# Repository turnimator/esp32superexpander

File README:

ESP32Superexpander.2ndattempt  - Previous hardware definition (KiCad) files
ESP32forth-7-Superexpander-0.1 - Arduino sketch containing a Superexpander ESPforth version
ESP32superexpander       -  The current Kicad files
Superexpander            - Arduino library for Suoerexpander
SuperExpander.odt        - A description of the project
superexpanderSupport.c   - Code to add to ESP32forth 

A document explaining the Forth code:

https://docs.google.com/document/d/1MlfXAm6yeVxjHgzF-E0LGG0kIZ7gFkiAXZAdYF-DrEk/edit?usp=sharing

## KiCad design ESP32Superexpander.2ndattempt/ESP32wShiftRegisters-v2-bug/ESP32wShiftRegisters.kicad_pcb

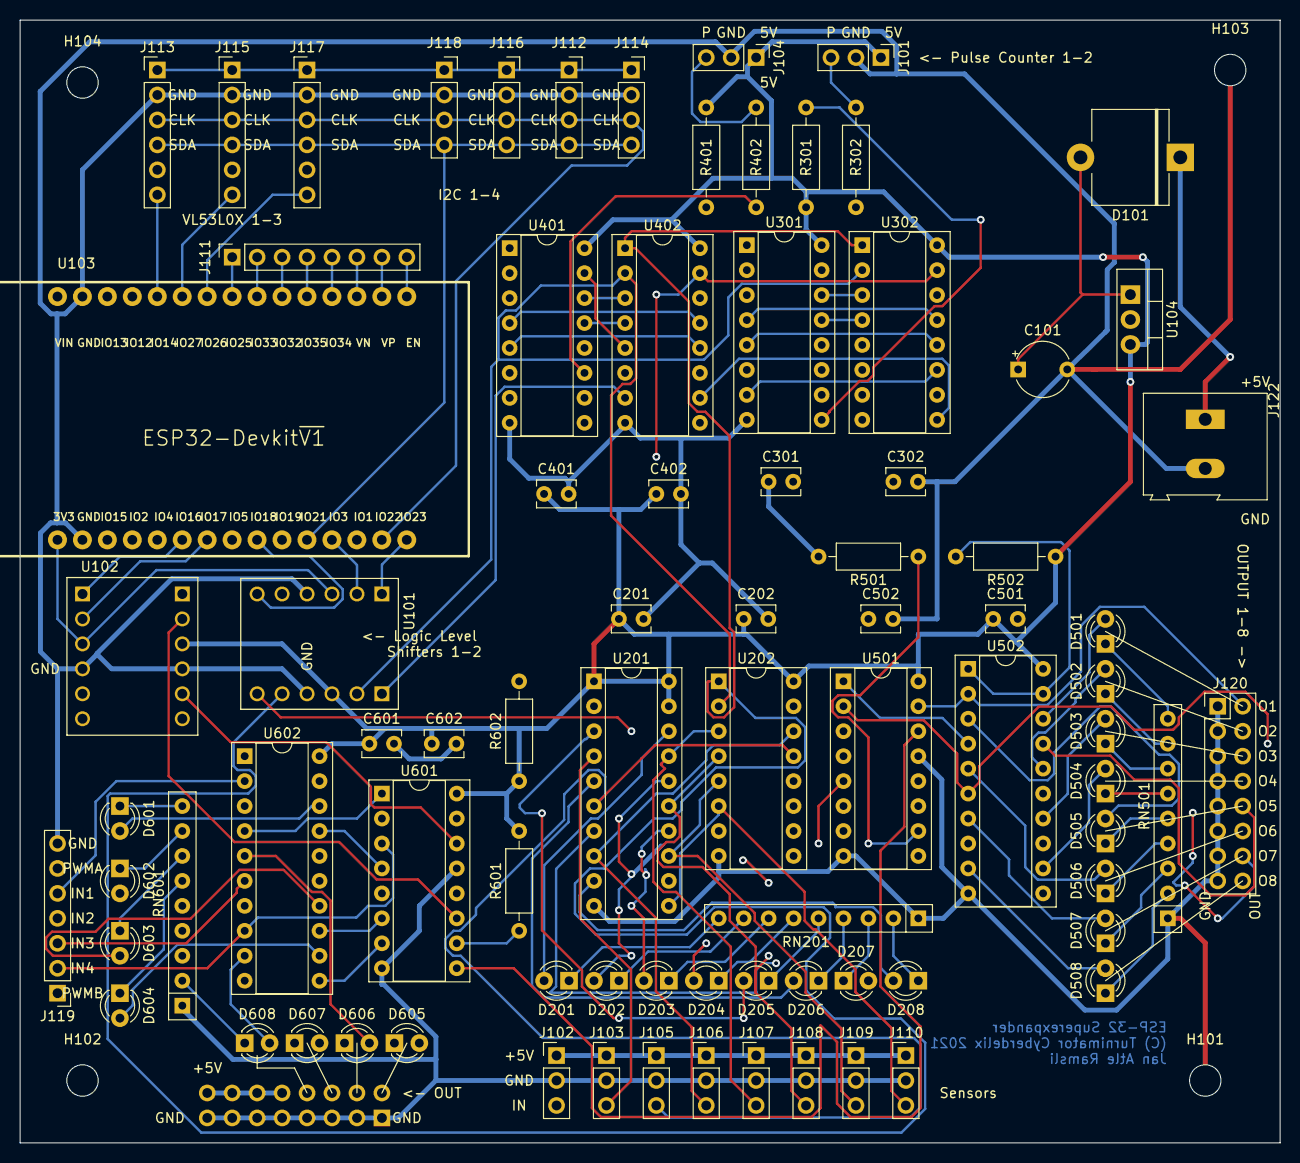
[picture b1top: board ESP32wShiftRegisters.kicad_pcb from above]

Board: 4 copper layers, 128.2 x 114.3 mm, 87 parts (1 on the bottom side), 137 nets.

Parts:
C101: 100uF; CP_Radial_Tantal_D5.5mm_P5.00mm
C201, C202: 100 nF; C_Disc_D3.8mm_W2.6mm_P2.50mm
C301, C302, C401, C402, C501, C502, C601, C602: 0.10uF; C_Disc_D3.8mm_W2.6mm_P2.50mm
D101: DIODE; D_5KP_P10.16mm_Horizontal
D201, D202, D203, D204, D205, D206, D207, D208, D501, D502, D503, D504, D505, D506, D507, D508, D601, D602, D603, D604, D605, D606, D607, D608: LED; LED_D3.0mm
H101, H102, H104: NC; MountingHole_3.2mm_M3
H103: GND; MountingHole_3.2mm_M3
J101: CNT1_in; PinHeader_1x03_P2.54mm_Vertical
J102: S1; PinHeader_1x03_P2.54mm_Vertical
J103: S2; PinHeader_1x03_P2.54mm_Vertical
J104: CNT2_in; PinHeader_1x03_P2.54mm_Vertical
J105: S3; PinHeader_1x03_P2.54mm_Vertical
J106: S4; PinHeader_1x03_P2.54mm_Vertical
J107: S5; PinHeader_1x03_P2.54mm_Vertical
J108: S6; PinHeader_1x03_P2.54mm_Vertical
J109: S7; PinHeader_1x03_P2.54mm_Vertical
J110: S8; PinHeader_1x03_P2.54mm_Vertical
J111: EN VP VN 34 35 32 33 25; PinSocket_1x08_P2.54mm_Vertical
J112, J116, J118: I2C; PinSocket_1x04_P2.54mm_Vertical
J113: VL53L0X_1; PinHeader_1x06_P2.54mm_Vertical
J114: i2C; PinSocket_1x04_P2.54mm_Vertical
J115: VL53L0X_2; PinHeader_1x06_P2.54mm_Vertical
J117: VL53L0X_3; PinHeader_1x06_P2.54mm_Vertical
J119: L298; PinHeader_1x07_P2.54mm_Vertical
J120: OUTPUT->; PinHeader_2x08_P2.54mm_Vertical
J121: Conn_02x08_Odd_Even; PinHeader_2x08_P2.54mm_Vertical
J122: 5V POWER; TerminalBlock_Altech_AK300-2_P5.00mm
R301, R302, R401, R402, R501, R502, R601, R602: 10k; R_Axial_DIN0207_L6.3mm_D2.5mm_P10.16mm_Horizontal
RN201, RN501, RN601: 220 R; R_Array_SIP9
U101, U102: BOB-12009; CONV_BOB-12009
U103: ESP32DEVKITV1; ESP32-DEVKITV1
U104: L7805; TO-220-3_Vertical
U201, U502, U602: 74HC244; DIP-20_W7.62mm_Socket
U202, U302, U402: 74LS165; DIP-16_W7.62mm_Socket
U301, U401: CD4060BE; DIP-16_W7.62mm_Socket
U501, U601: 74LS595; DIP-16_W7.62mm_Socket

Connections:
3VCNT_RESET: U102.LV4, U103.28
3VP2S_CE: U101.LV4, U103.9
3VP2S_SCK: U101.LV2, U103.12
3VP2S_SDA: U101.LV1, U103.15
3VP2S_SHLD: U101.LV3, U103.10
3VS2P_LATCH: U102.LV1, U103.6
3VS2P_SCL: U102.LV2, U103.7
3VS2P_SDA: U102.LV3, U103.5
5V: C201.1, C202.1, C301.1, C302.1, C401.1, C402.1, C501.1, C502.1, C601.1, C602.1, J101.1, J102.1, J103.1, J104.1, J105.1, J106.1, J107.1, J108.1, J109.1, J110.1, J121.10, J121.12, J121.14, J121.16, R301.1, R401.1, R501.2, R502.1, R601.2, R602.1, U101.HV, U102.HV, U103.30, U104.3, U201.1, U201.19, U201.20, U202.16, U301.16, U302.16, U401.16, U402.16, U501.16, U502.20, U601.16, U602.20
+3V: J112.1, J113.1, J114.1, J115.1, J116.1, J117.1, J118.1, U101.LV, U102.LV, U103.1
+5V: D101.1, J122.1
/Actuator1/OUT0: J120.2, U501.15, U502.2
/Actuator1/OUT1: J120.4, U501.1, U502.4
/Actuator1/OUT2: J120.6, U501.2, U502.6
/Actuator1/OUT3: J120.8, U501.3, U502.8
/Actuator1/OUT4: J120.10, U501.4, U502.17
/Actuator1/OUT5: J120.12, U501.5, U502.15
/Actuator1/OUT6: J120.14, U501.6, U502.13
/Actuator1/OUT7: J120.16, U501.7, U502.11
/Actuator1/SER_IN: U501.14, U601.9
/Counter1/CASC_IN: U202.9, U302.10
/Counter2/CASC_IN: U302.9, U402.10
/Motor Control/OUT4: J121.2, U601.4, U602.17
/Motor Control/OUT5: J121.4, U601.5, U602.15
/Motor Control/OUT6: J121.6, U601.6, U602.13
/Motor Control/OUT7: J121.8, U601.7, U602.11
CNT1_IN: J101.3, R302.1
CNT2_IN: J104.3, R402.1
CNT_RESET: U102.HV4, U301.12, U401.12
EN: J111.8, U103.16
GND: C101.2, C201.2, C202.2, C301.2, C302.2, C401.2, C402.2, C501.2, C502.2, C601.2, C602.2, H101.1, H103.1, J101.2, J102.2, J103.2, J104.2, J105.2, J106.2, J107.2, J108.2, J109.2, J110.2, J112.2, J113.2, J114.2, J115.2, J116.2, J117.2, J118.2, J119.7, J120.1, J120.3, J120.5, J120.7, J120.9, J120.11, J120.13, J120.15, J121.1, J121.3, J121.5, J121.7, J121.9, J121.11, J121.13, J121.15, J122.2, RN201.1, RN501.1, RN601.1, U101.GND_1, U101.GND_2, U102.GND_1, U102.GND_2, U103.2, U103.29, U104.2, U201.10, U202.8, U301.8, U302.8, U401.8, U402.8, U501.8, U501.13, U502.10, U601.8, U601.13, U602.10
I2C_SCL: J112.3, J113.3, J114.3, J115.3, J116.3, J117.3, J118.3, U103.14
I2C_SDA: J112.4, J113.4, J114.4, J115.4, J116.4, J117.4, J118.4, U103.11
IN1: J119.5, U601.15, U602.2
IN2: J119.4, U601.1, U602.4
IN3: J119.3, U601.2, U602.6
IN4: J119.2, U601.3, U602.8
IO25: J111.1, U103.23
IO32: J111.3, U103.21
IO33: J111.2, U103.22
IO34: J111.5, U103.19
IO35: J111.4, U103.20
M_PWMA: J119.6, U103.3
M_PWMB: J119.1, U103.8
unnamed: C101.1, D101.2, U104.1
unnamed: D201.1, RN201.9
unnamed: D201.2, U201.18
unnamed: D202.1, RN201.8
unnamed: D202.2, U201.16
unnamed: D203.1, RN201.7
unnamed: D203.2, U201.14
unnamed: D204.1, RN201.6
unnamed: D204.2, U201.12
unnamed: D205.1, RN201.5
unnamed: D205.2, U201.3
unnamed: D206.1, RN201.4
unnamed: D206.2, U201.5
unnamed: D207.1, RN201.3
unnamed: D207.2, U201.7
unnamed: D208.1, RN201.2
unnamed: D208.2, U201.9
unnamed: D501.1, RN501.9
unnamed: D501.2, U502.18
unnamed: D502.1, RN501.8
unnamed: D502.2, U502.16
unnamed: D503.1, RN501.7
unnamed: D503.2, U502.14
unnamed: D504.1, RN501.6
unnamed: D504.2, U502.12
unnamed: D505.1, RN501.5
unnamed: D505.2, U502.3
unnamed: D506.1, RN501.4
unnamed: D506.2, U502.5
unnamed: D507.1, RN501.3
unnamed: D507.2, U502.7
unnamed: D508.1, RN501.2
unnamed: D508.2, U502.9
unnamed: D601.1, RN601.9
unnamed: D601.2, U602.18
unnamed: D602.1, RN601.8
unnamed: D602.2, U602.16
unnamed: D603.1, RN601.7
unnamed: D603.2, U602.14
unnamed: D604.1, RN601.6
unnamed: D604.2, U602.12
unnamed: D605.1, RN601.5
unnamed: D605.2, U602.3
unnamed: D606.1, RN601.4
unnamed: D606.2, U602.5
unnamed: D607.1, RN601.3
unnamed: D607.2, U602.7
unnamed: D608.1, RN601.2
unnamed: D608.2, U602.9
unnamed: R301.2, U301.9
unnamed: R302.2, U301.11
unnamed: R401.2, U401.9
unnamed: R402.2, U401.11
unnamed: R501.1, U501.10
unnamed: R502.2, U502.1, U502.19
unnamed: R601.1, U601.10
unnamed: R602.2, U602.1, U602.19
unnamed: U301.1, U302.6
unnamed: U301.4, U302.13
unnamed: U301.5, U302.12
unnamed: U301.6, U302.14
unnamed: U301.7, U302.11
unnamed: U301.13, U302.4
unnamed: U301.14, U302.3
unnamed: U301.15, U302.5
unnamed: U401.1, U402.6
unnamed: U401.4, U402.13
unnamed: U401.5, U402.12
unnamed: U401.6, U402.14
unnamed: U401.7, U402.11
unnamed: U401.13, U402.4
unnamed: U401.14, U402.3
unnamed: U401.15, U402.5
P2S_CE: U101.HV4, U202.15, U302.15, U402.15
P2S_SCK: U101.HV2, U202.2, U302.2, U402.2
P2S_SDA: U101.HV1, U402.7
P2S_SHLD: U101.HV3, U202.1, U302.1, U402.1
S2P_LATCH: U102.HV1, U501.12, U601.12
S2P_SCL: U102.HV2, U501.11, U601.11
S2P_SDA: U102.HV3, U601.14
SENSOR0: J102.3, U201.2, U202.11
SENSOR1: J103.3, U201.4, U202.12
SENSOR2: J105.3, U201.6, U202.13
SENSOR3: J106.3, U201.8, U202.14
SENSOR4: J107.3, U201.17, U202.3
SENSOR5: J108.3, U201.15, U202.4
SENSOR6: J109.3, U201.13, U202.5
SENSOR7: J110.3, U201.11, U202.6
VN: J111.6, U103.18
VP: J111.7, U103.17
XSHUT1: J113.6, U103.26
XSHUT2: J115.6, U103.25
XSHUT3: J117.6, U103.24

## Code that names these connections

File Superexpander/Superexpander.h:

struct InputRegister
{
  byte unused;
  byte counter1; 
  byte counter2;
  byte sensors;   //8 on-off sensors
} input_register;

class Superexpander
{
    const int p2s_data_pin = 23; // Connect Pin 11 to SER_OUT (Serial data out) - Pin 9 (Q7) of 74HC165
    const int p2s_shld_pin = 19; // Connect Pin 8 to SH/!LD (shift or active low load) - Pin 1 (!PL) of 74HC165
    const int p2s_clk_pin = 17; // Connect Pin 12 to CLK (the clock that times the shifting) - Pin 2 (CP) of 74HC165
    const int p2s_ce_pin = 18; // Connect Pin 9 to !CE (clock enable, active low) - Pin 15 (!CE) of 74HC165
    const int counter_reset_pin = 13;
    const int s2p_sda_pin = 4;
    const int s2p_scl_pin = 17;
    const int s2p_latch_pin = 16;

    uint16_t output_register = 0; // 16 on-off output switches

  protected:

    uint32_t shiftInN(int sda, int sck, boolean xsb, int nBits)
    {
      uint32_t rv;
      rv = 0;

      for (int i = 0; i < nBits; i++) {
        digitalWrite(sck, HIGH);
        delayMicroseconds(5);
        int b = digitalRead(sda);
        if (xsb == MSBFIRST) {
          rv |= b << i;
        } else {
          rv |= b << (nBits - i);
        }
        digitalWrite(sck, LOW);
        delayMicroseconds(5);
      }

      return rv;
    }


  public:
    
 
    inline void setSwitch(int n, boolean b)
    {
      if (b)
        output_register |= (1 << n);
      else
        output_register &= ~(1 << n);
    }

    inline void setMotor(boolean left_forward, boolean right_forward)
    {
      if (left_forward){
        setSwitch(0, true);
        setSwitch(1, false);
      } else {
        setSwitch(0, false);
        setSwitch(1, true);
      }
      if (right_forward){
        setSwitch(2, true);
        setSwitch(3, false);
      } else {
        setSwitch(2, false);
        setSwitch(3, true);
      }

    }
    
    inline int getCounter1()
    {
      return input_register.counter1;
    }

    inline int getCounter2()
    {
      return input_register.counter2;
    }


   inline bool getSensor(int n)
    {
      return input_register.sensors&(1<<n);
    }
 

    void begin()
    {
      pinMode(p2s_shld_pin, OUTPUT);
      pinMode(p2s_ce_pin, OUTPUT);
      pinMode(p2s_clk_pin, OUTPUT);
      pinMode(p2s_data_pin, INPUT);
      pinMode(counter_reset_pin, OUTPUT);

      pinMode(s2p_sda_pin, OUTPUT);
     // pinMode(s2p_scl_pin, OUTPUT); // Not necessary. Same as p2s_clk_pin
      pinMode(s2p_latch_pin, OUTPUT);

      digitalWrite(counter_reset_pin, HIGH);
      delay(20);
      digitalWrite(counter_reset_pin, LOW);
      // Required initial states of these two pins according to the datasheet timing diagram
      digitalWrite(p2s_clk_pin, HIGH);
      digitalWrite(p2s_shld_pin, HIGH);
      Serial.println("Turnimator Cyberdelix\nSuperexpander v.01 initialized");

    }

    void writeBoard()
    {
      byte hibyte = (output_register >> 8) & 0xff;
      byte lowbyte = output_register & 0xff;

      digitalWrite(s2p_latch_pin, 0);
      shiftOut(s2p_sda_pin, s2p_scl_pin, MSBFIRST, hibyte);
      shiftOut(s2p_sda_pin, s2p_scl_pin, MSBFIRST, lowbyte);
      digitalWrite(s2p_latch_pin, 1);
    }

    void readBoard()
    {

      digitalWrite(p2s_shld_pin, LOW); // Load data
      delayMicroseconds(5);
      digitalWrite(p2s_shld_pin, HIGH);
      delayMicroseconds(5);
      digitalWrite(p2s_clk_pin, HIGH);
      digitalWrite(p2s_ce_pin, LOW); // Enable the clock
      input_register.counter1 = ~shiftIn(p2s_data_pin, p2s_clk_pin, MSBFIRST);
      input_register.counter2 = ~shiftIn(p2s_data_pin, p2s_clk_pin, MSBFIRST);
      input_register.sensors = shiftIn(p2s_data_pin, p2s_clk_pin, MSBFIRST);

      digitalWrite(p2s_ce_pin, HIGH); // Disable the clock
    }

};

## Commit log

2022-02-18 Second commit
2022-02-18 Upgraded to 7.054
2022-02-27 Complete Project
2022-02-27 Added README
2022-04-22 Added Forth code
2022-04-28 Finished slides
2022-05-03 Last slide
2022-05-03 Added motor.fs
2022-05-04 Added tickleme
